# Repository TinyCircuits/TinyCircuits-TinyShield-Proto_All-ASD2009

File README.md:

# TinyCircuits TinyShield Proto All Board
# ASD2009 Rev1

The design files are located under design_files/ for the TinyCircuits ASD2009 Rev 1 PCB.  This is a Tiny shield board (Square Version, 20mm x 20mm) that has all of the shield signals brought out to 0.1" spaced holes. 

Format is in Cadsoft Eagle format - Eagle version 6.2 was used for the original design.

For more infomation on this, check out the product page at TinyCircuits.com: https://tinycircuits.com/collections/proto-boards/products/proto-board-tinyshield?variant=14984618823

# License:

Design by TinyCircuits.
All design files are released under the Creative Commons Attribution Share-Alike 3.0 License, see the following link for details: http://creativecommons.org/licenses/by-sa/3.0

All text above must be included in any redistribution or derived design

This project uses designs and concepts developed as part of the Arduino project and the LilyPad project.  The TinyCircuits design files themselves (schematics, PCB and libraries) are not directly derived from these works' design files and have been created new, however the concepts and basic architecture behind the TinyDuino and TinyLily products are derived and we thank the hard work of the organizations below for their contributions to open-source hardware:
  
Original Arduino Uno Design by Team Arduino

LilyPad Arduino Design by Leah Buechley and Sparkfun Electronics

Please support the open-source hardware community

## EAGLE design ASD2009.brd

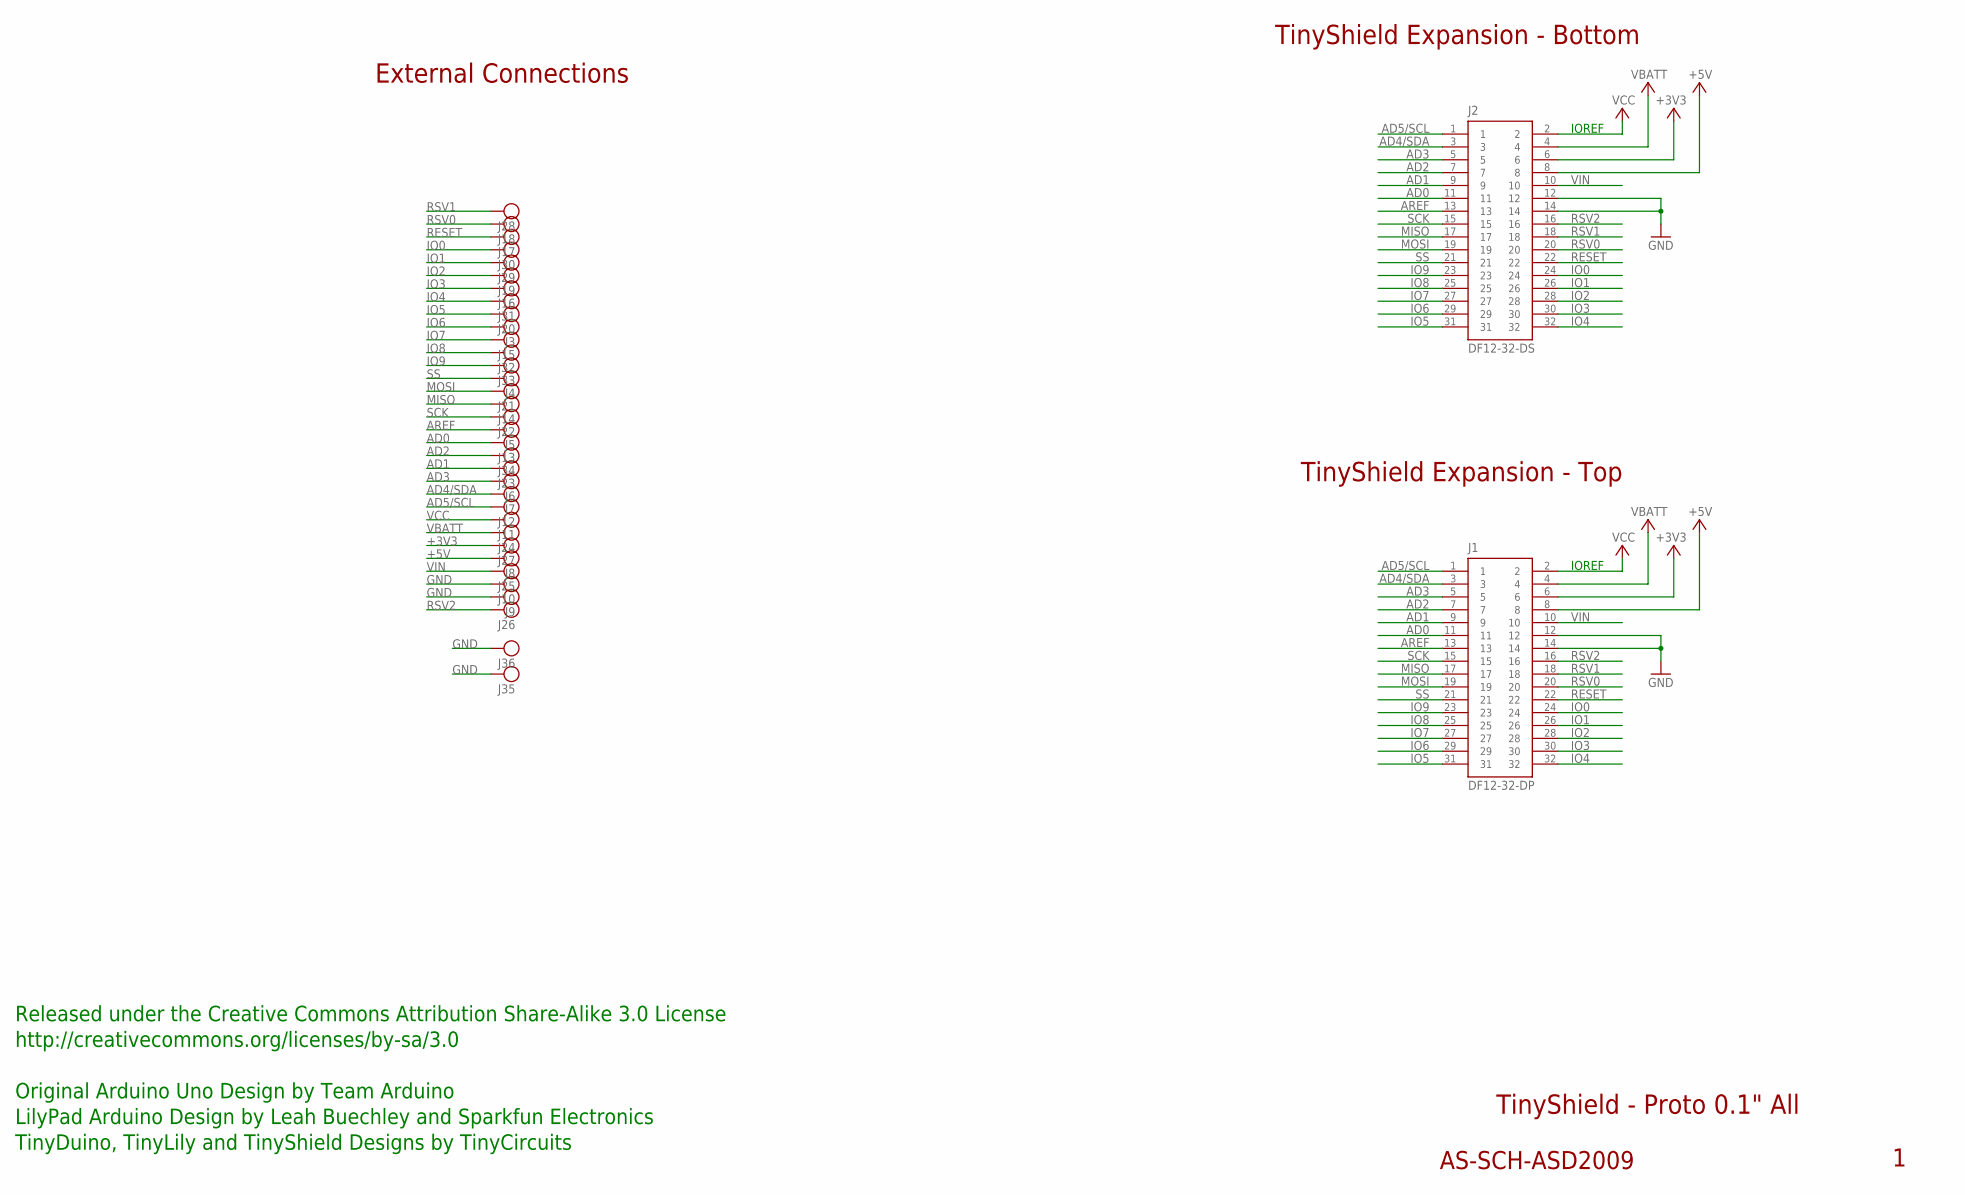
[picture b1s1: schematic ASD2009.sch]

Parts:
J1: DF12-32-DP; PARTNO AS-ITM-00015
J2: DF12-32-DS; PARTNO AS-ITM-00012
J3, J4, J5, J6, J7, J8, J9, J10, J11, J12, J13, J14, J15, J16, J17, J18, J19, J20, J21, J22, J23, J24, J25, J26, J27, J28, J29, J30, J31, J32, J33, J34, J35, J36: PIN_1X.1"1; 1X.1"_2

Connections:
+3V3: J1.6, J2.6, J27.1
+5V: J1.8, J2.8, J8.1
AD0: J1.11, J2.11, J13.1
AD1: J1.9, J2.9, J23.1
AD2: J1.7, J2.7, J34.1
AD3: J1.5, J2.5, J6.1
AD4/SDA: J1.3, J2.3, J7.1
AD5/SCL: J1.1, J2.1, J12.1
AREF: J1.13, J2.13, J5.1
GND: J1.12, J1.14, J2.12, J2.14, J9.1, J10.1, J35.1, J36.1
IO0: J1.24, J2.24, J30.1
IO1: J1.26, J2.26, J29.1
IO2: J1.28, J2.28, J19.1
IO3: J1.30, J2.30, J16.1
IO4: J1.32, J2.32, J31.1
IO5: J1.31, J2.31, J20.1
IO6: J1.29, J2.29, J3.1
IO7: J1.27, J2.27, J15.1
IO8: J1.25, J2.25, J32.1
IO9: J1.23, J2.23, J33.1
MISO: J1.17, J2.17, J14.1
MOSI: J1.19, J2.19, J21.1
RESET: J1.22, J2.22, J17.1
RSV0: J1.20, J2.20, J18.1
RSV1: J1.18, J2.18, J28.1
RSV2: J1.16, J2.16, J26.1
SCK: J1.15, J2.15, J22.1
SS: J1.21, J2.21, J4.1
VBATT: J1.4, J2.4, J24.1
VCC: J1.2, J2.2, J11.1
VIN: J1.10, J2.10, J25.1

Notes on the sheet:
TinyShield Expansion - Bottom
TinyShield - Proto 0.1" All
AS-SCH-ASD2009
TinyShield Expansion - Top
IOREF
Released under the Creative Commons Attribution Share-Alike 3.0 License
http://creativecommons.org/licenses/by-sa/3.0
LilyPad Arduino Design by Leah Buechley and Sparkfun Electronics
TinyDuino, TinyLily and TinyShield Designs by TinyCircuits
Original Arduino Uno Design by Team Arduino
External Connections

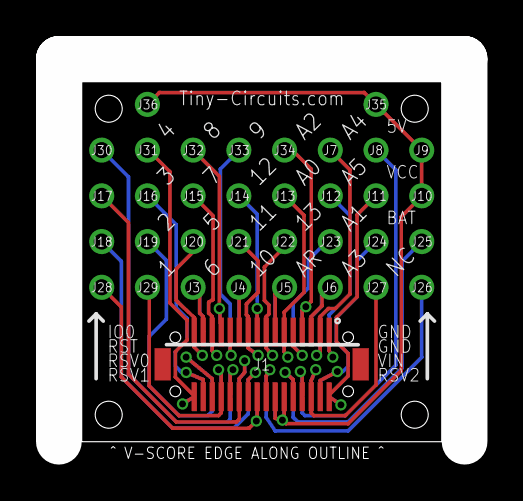
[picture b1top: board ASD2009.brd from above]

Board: 2 copper layers, 20.0 x 20.0 mm, 37 parts (1 on the bottom side), 31 nets.

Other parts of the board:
U$1: DOCFIELD-TINYCIRCUITS-PCB

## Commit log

2015-02-22 :lollipop: Added .gitattributes & .gitignore files
2015-02-22 Updated link
2019-01-04 Update format
2020-07-28 Add CAD data
2020-08-14 Update CAD drawing
